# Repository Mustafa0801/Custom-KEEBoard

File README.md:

# Custom-KEEBoard

I created a normal and basic keyboard for this project. It does not have any extra parts like LEDs (though I did try to add those initially).  
  \
This project was my first experience with hardware like PCBs, microcontrollers, how to wire things together and stuff like that.
I've always been more interested in the software side of things however making a keyboard, albeit with a LOT of help, was still really fun.
It showed me how complex things really are that allow us to do the simple tasks we're so used to, even now as I'm typing this it's only possible because of the technical ingenuity of those who created and designed the keyboard.  
  \
The main issues I faced in this project was how overwhelming things felt at times, using new software and reading paragraphs of things which make no sense to you at all.
But in the end I'm quite happy with what I was able to achieve, even though it was a simple keyboard for my first adventure into this field.

Onshape link: https://cad.onshape.com/documents/56a54eae4c7e48d4d39df1fe/w/475236177727db4b95dad126/e/836049768bea304fa6717bf7?renderMode=0&uiState=6ae73c4305ffe80012acf5dc  
and the Case with one switch for reference, adding all switches was taking too much time

  \
Aand heres the BOM:
  \

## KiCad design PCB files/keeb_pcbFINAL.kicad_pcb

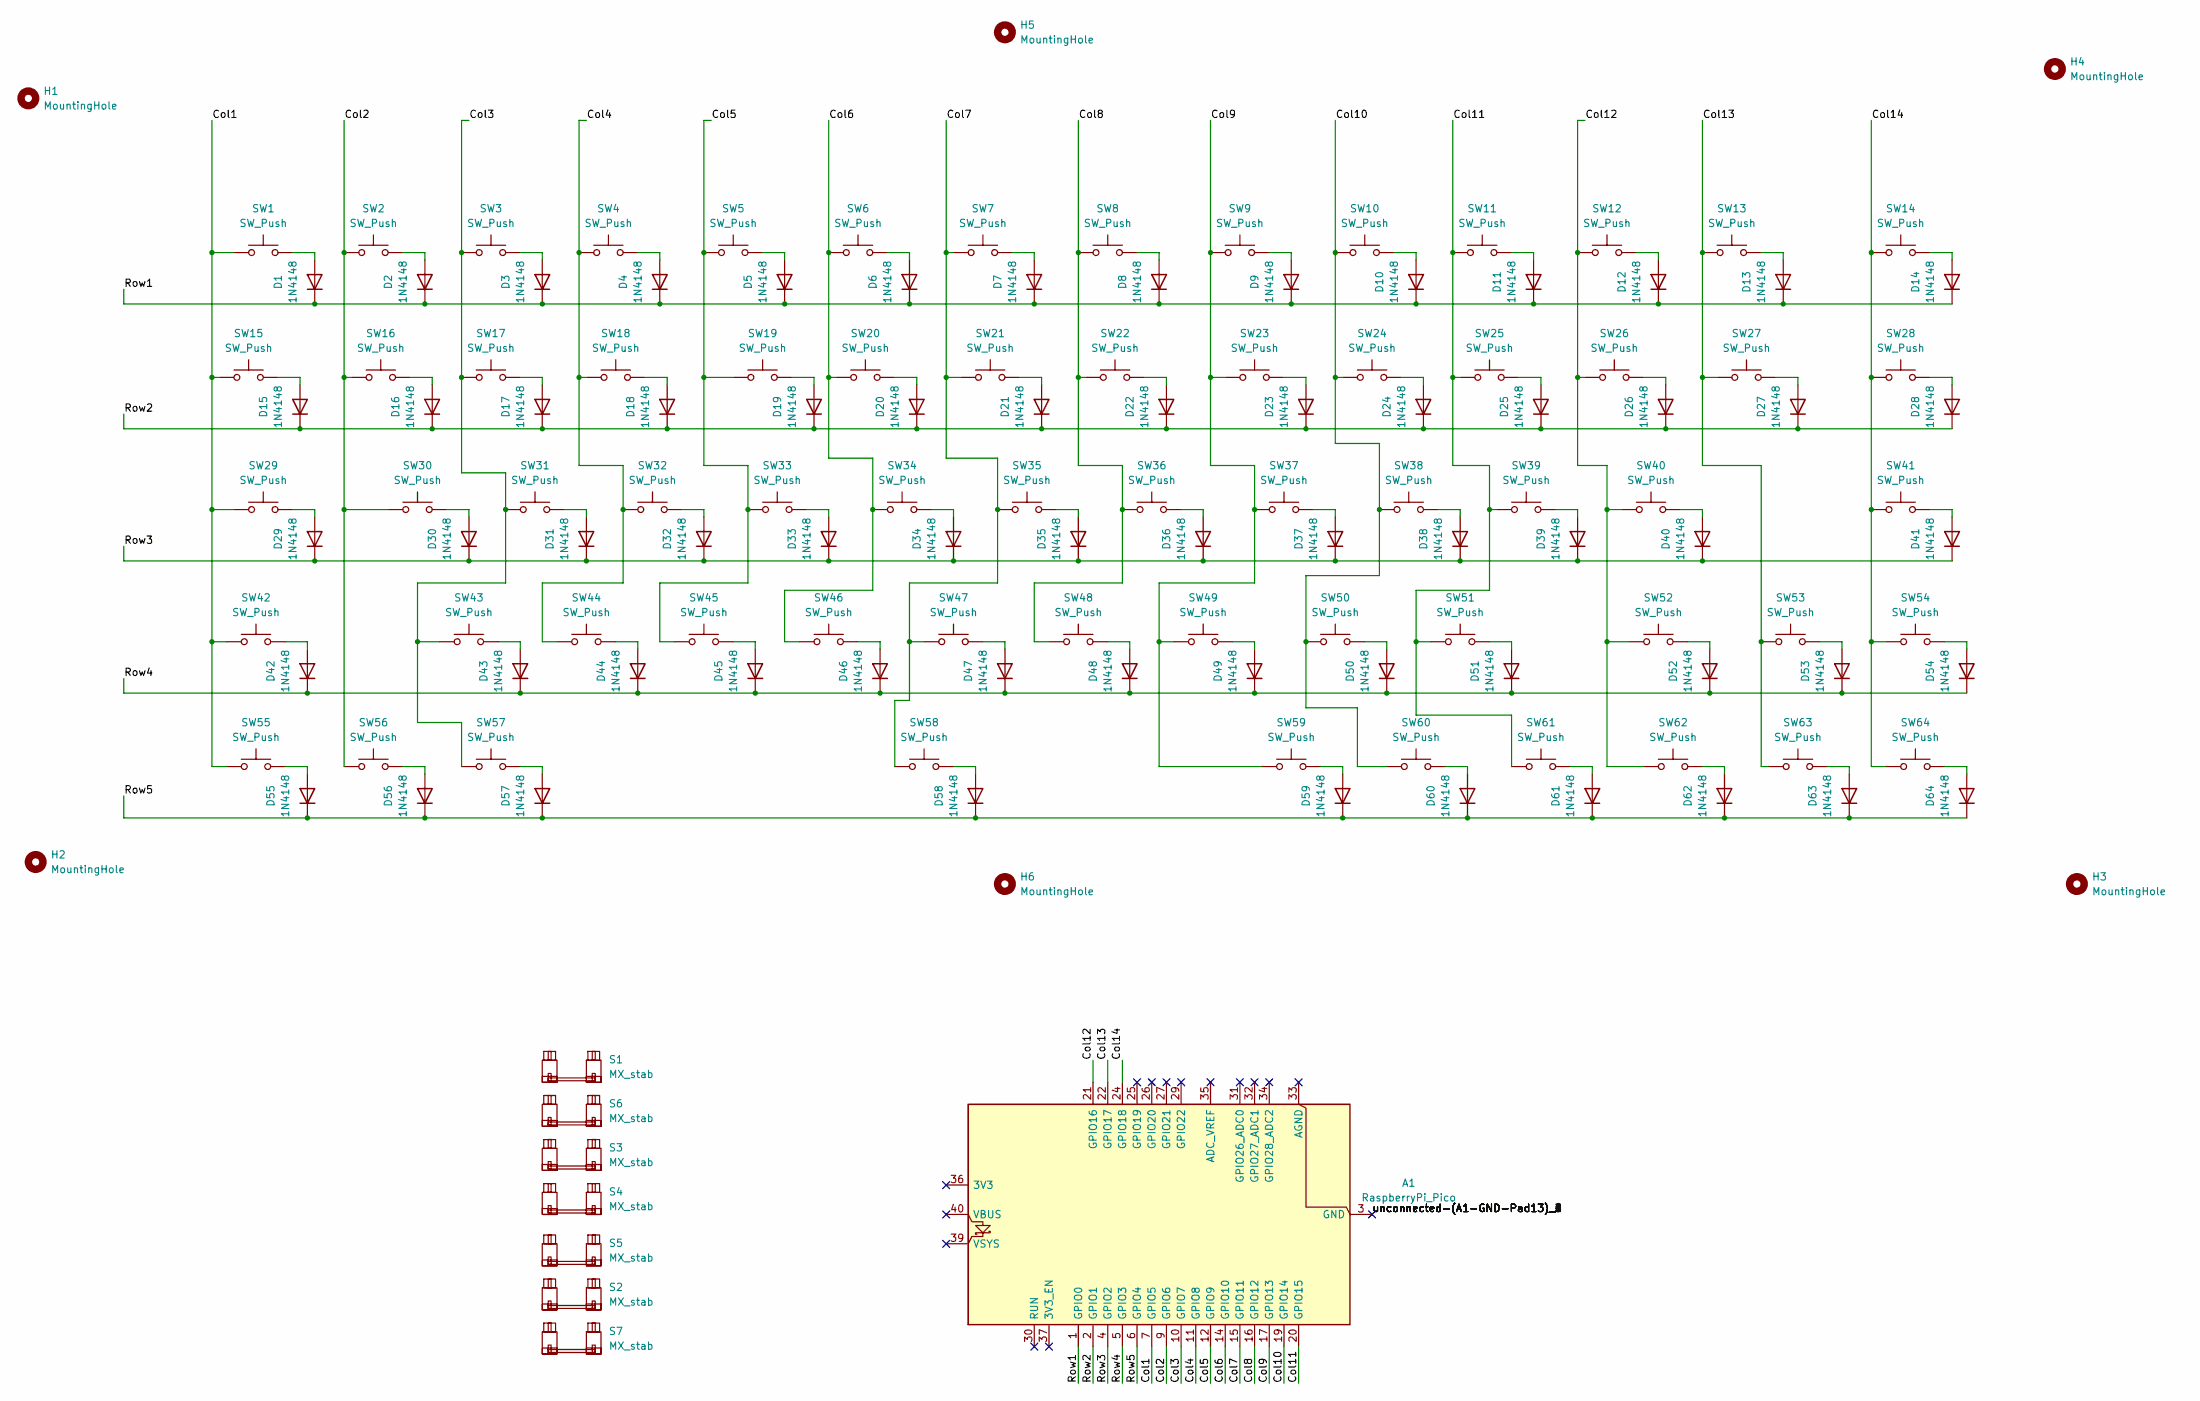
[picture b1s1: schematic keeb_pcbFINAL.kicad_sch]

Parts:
A1: RaspberryPi_Pico; RaspberryPi_Pico_Common_THT
D1, D2, D3, D4, D5, D6, D7, D8, D9, D10, D11, D12, D13, D14, D15, D16, D17, D18, D19, D20, D21, D22, D23, D24, D25, D26, D27, D28, D29, D30, D31, D32, D33, D34, D35, D36, D37, D38, D39, D40, D41, D42, D43, D44, D45, D46, D47, D48, D49, D50, D51, D52, D53, D54, D55, D56, D57, D58, D59, D60, D61, D62, D63, D64: 1N4148; D_DO-35_SOD27_P7.62mm_Horizontal
H1, H2, H3, H4, H5, H6: MountingHole; Maple_Mini
S1, S2, S4, S5: MX_stab; STAB_MX_2.25u
S3, S6: MX_stab; STAB_MX_2u
S7: MX_stab; STAB_MX_6.25u
SW1, SW2, SW3, SW4, SW5, SW6, SW7, SW8, SW9, SW10, SW11, SW12, SW13, SW14, SW15, SW16, SW17, SW18, SW19, SW20, SW21, SW22, SW23, SW24, SW25, SW26, SW27, SW28, SW29, SW30, SW31, SW32, SW33, SW34, SW35, SW36, SW37, SW38, SW39, SW40, SW41, SW42, SW43, SW44, SW45, SW46, SW47, SW48, SW49, SW50, SW51, SW52, SW53, SW54, SW55, SW56, SW57, SW58, SW59, SW60, SW61, SW62, SW63, SW64: SW_Push; SW_MX_1u

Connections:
/Col1: A1.7 (GPIO5), SW1.1, SW15.1, SW29.1, SW42.1, SW55.1
/Col2: A1.9 (GPIO6), SW2.1, SW16.1, SW30.1, SW56.1
/Col3: A1.10 (GPIO7), SW3.1, SW17.1, SW31.1, SW43.1, SW57.1
/Col4: A1.11 (GPIO8), SW4.1, SW18.1, SW32.1, SW44.1
/Col5: A1.12 (GPIO9), SW5.1, SW19.1, SW33.1, SW45.1
/Col6: A1.14 (GPIO10), SW6.1, SW20.1, SW34.1, SW46.1
/Col7: A1.15 (GPIO11), SW7.1, SW21.1, SW35.1, SW47.1, SW58.1
/Col8: A1.16 (GPIO12), SW8.1, SW22.1, SW36.1, SW48.1
/Col9: A1.17 (GPIO13), SW9.1, SW23.1, SW37.1, SW49.1, SW59.1
/Col10: A1.19 (GPIO14), SW10.1, SW24.1, SW38.1, SW50.1, SW60.1
/Col11: A1.20 (GPIO15), SW11.1, SW25.1, SW39.1, SW51.1, SW61.1
/Col12: A1.21 (GPIO16), SW12.1, SW26.1, SW40.1, SW52.1, SW62.1
/Col13: A1.22 (GPIO17), SW13.1, SW27.1, SW53.1, SW63.1
/Col14: A1.24 (GPIO18), SW14.1, SW28.1, SW41.1, SW54.1, SW64.1
/Row1: A1.1 (GPIO0), D1.1 (K), D2.1 (K), D3.1 (K), D4.1 (K), D5.1 (K), D6.1 (K), D7.1 (K), D8.1 (K), D9.1 (K), D10.1 (K), D11.1 (K), D12.1 (K), D13.1 (K), D14.1 (K)
/Row2: A1.2 (GPIO1), D15.1 (K), D16.1 (K), D17.1 (K), D18.1 (K), D19.1 (K), D20.1 (K), D21.1 (K), D22.1 (K), D23.1 (K), D24.1 (K), D25.1 (K), D26.1 (K), D27.1 (K), D28.1 (K)
/Row3: A1.4 (GPIO2), D29.1 (K), D30.1 (K), D31.1 (K), D32.1 (K), D33.1 (K), D34.1 (K), D35.1 (K), D36.1 (K), D37.1 (K), D38.1 (K), D39.1 (K), D40.1 (K), D41.1 (K)
/Row4: A1.5 (GPIO3), D42.1 (K), D43.1 (K), D44.1 (K), D45.1 (K), D46.1 (K), D47.1 (K), D48.1 (K), D49.1 (K), D50.1 (K), D51.1 (K), D52.1 (K), D53.1 (K), D54.1 (K)
/Row5: A1.6 (GPIO4), D55.1 (K), D56.1 (K), D57.1 (K), D58.1 (K), D59.1 (K), D60.1 (K), D61.1 (K), D62.1 (K), D63.1 (K), D64.1 (K)
unnamed: D1.2 (A), SW1.2
unnamed: D2.2 (A), SW2.2
unnamed: D3.2 (A), SW3.2
unnamed: D4.2 (A), SW4.2
unnamed: D5.2 (A), SW5.2
unnamed: D6.2 (A), SW6.2
unnamed: D7.2 (A), SW7.2
unnamed: D8.2 (A), SW8.2
unnamed: D9.2 (A), SW9.2
unnamed: D10.2 (A), SW10.2
unnamed: D11.2 (A), SW11.2
unnamed: D12.2 (A), SW12.2
unnamed: D13.2 (A), SW13.2
unnamed: D14.2 (A), SW14.2
unnamed: D15.2 (A), SW15.2
unnamed: D16.2 (A), SW16.2
unnamed: D17.2 (A), SW17.2
unnamed: D18.2 (A), SW18.2
unnamed: D19.2 (A), SW19.2
unnamed: D20.2 (A), SW20.2
unnamed: D21.2 (A), SW21.2
unnamed: D22.2 (A), SW22.2
unnamed: D23.2 (A), SW23.2
unnamed: D24.2 (A), SW24.2
unnamed: D25.2 (A), SW25.2
unnamed: D26.2 (A), SW26.2
unnamed: D27.2 (A), SW27.2
unnamed: D28.2 (A), SW28.2
unnamed: D29.2 (A), SW29.2
unnamed: D30.2 (A), SW30.2
unnamed: D31.2 (A), SW31.2
unnamed: D32.2 (A), SW32.2
unnamed: D33.2 (A), SW33.2
unnamed: D34.2 (A), SW34.2
unnamed: D35.2 (A), SW35.2
unnamed: D36.2 (A), SW36.2
unnamed: D37.2 (A), SW37.2
unnamed: D38.2 (A), SW38.2
unnamed: D39.2 (A), SW39.2
unnamed: D40.2 (A), SW40.2
unnamed: D41.2 (A), SW41.2
unnamed: D42.2 (A), SW42.2
unnamed: D43.2 (A), SW43.2
unnamed: D44.2 (A), SW44.2
unnamed: D45.2 (A), SW45.2
unnamed: D46.2 (A), SW46.2
unnamed: D47.2 (A), SW47.2
unnamed: D48.2 (A), SW48.2
unnamed: D49.2 (A), SW49.2
unnamed: D50.2 (A), SW50.2
unnamed: D51.2 (A), SW51.2
unnamed: D52.2 (A), SW52.2
unnamed: D53.2 (A), SW53.2
unnamed: D54.2 (A), SW54.2
unnamed: D55.2 (A), SW55.2
unnamed: D56.2 (A), SW56.2
unnamed: D57.2 (A), SW57.2
unnamed: D58.2 (A), SW58.2
unnamed: D59.2 (A), SW59.2
unnamed: D60.2 (A), SW60.2
unnamed: D61.2 (A), SW61.2
unnamed: D62.2 (A), SW62.2
unnamed: D63.2 (A), SW63.2
unnamed: D64.2 (A), SW64.2

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
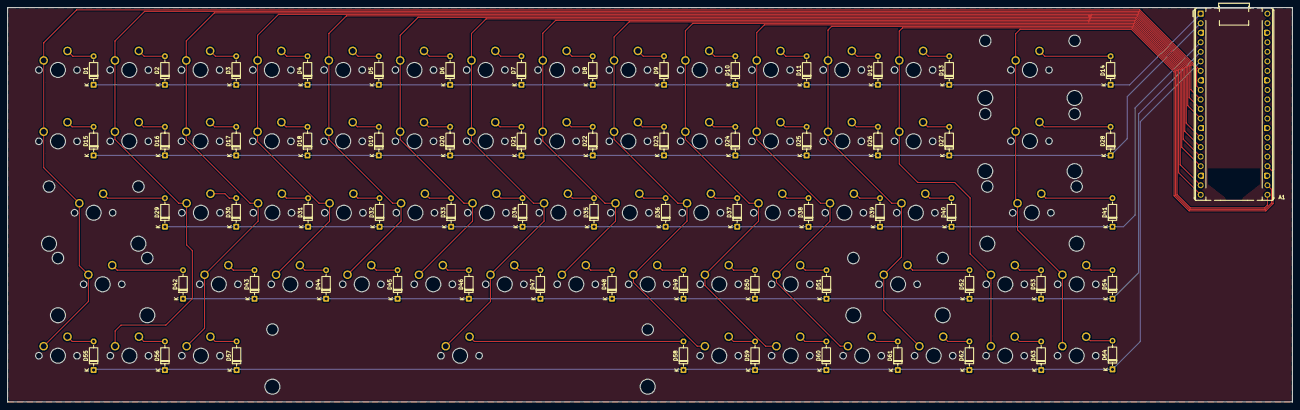
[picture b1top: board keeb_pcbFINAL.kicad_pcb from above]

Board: 2 copper layers, 342.4 x 105.1 mm, 136 parts (0 on the bottom side), 83 nets.
